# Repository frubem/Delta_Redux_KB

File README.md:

# DELTA Redux Keyboard

## DISCLAIMER

Any use of this project is **under your own responsibility**.
By using this project You will agree that I cannot be held responsible if it will destroy any of your devices, damage your computer, burn down your house or whatever.

### Sponsorship

This project is sponsored by [PCBWay](https://pcbway.com).
PCBWay specializes in manufacturing high-quality PCBs and makes them affordable to hobbyist and professionals alike.

The range of services they offer include PCB prototyping, assembly, instant quotes for your order, a verification process by a team
of experts and an easy to use, hassle-free order process.

Thanks to PCBWay, I was able to bring this project to production and to release it for everyone to use much earlier than it would have been possible otherwise.

## Introduction

This projects aims to create an ASCII keyboard tailored for use on to the [DELTA](https://codeberg.org/hkzlab/NE_Delta_Schematics) computer.
The work is based off the [Replica Datanetics Keyboard](https://github.com/schlae/replica-datanetics) by [Tube Time](https://mastodon.social/@tubetime), but sporting a different PCB, a modified circuit and firmware.

This keyboard supports uppercase and lowercase characters, both the strobe and AKD signals and caps-lock functionality (without using a mechanical latch), and can be built with your Cherry MX compatible switches of choice!

### Features

- Supports upper and lowercase characters
- Reset can be performed either with the reset button alone, or with the CTRL-Reset combination, depending on a jumper
- Caps lock without a mechanical latch
- Repeat key with adjustable frequency
- AKD signal
- External numeric keypad support
- 5 "extra" keys that can send custom strings to the attached machines

#### The "extra" keys

The "extra" keys are keys that simply trigger an automatic transmission of a string to the host computer, a macro. The strings are baked into the MCU, and the [firmware](fw/main.c) must be recompiled to change them.

The default strings are:
1. `PR#3\r`: Enables 80 column mode
2. `PR#6\r`: Boots card on slot 6
3. `CATALOG\r`: DOS command to list files on floppy
4. `CALL 65385\r`: When inside the BASIC interpreter, this will switch to the monitor
5. `03F4:00\rFA69G\r`: When inside the monitor, this will force a cold-reset

**Note that the optional numpad is still work-in-progress!**

### Support

If you wish to support me in building new hardware and software for old machines, [throw a few euros in my direction via Ko-Fi](https://ko-fi.com/hkzlab) ☕!

## Build one!

### Order the PCBs

You can find the gerbers in this repository, or you can order the PCBs at **PCBWay!**

You will one of each of the following:

- The [keyboard base](https://www.pcbway.com/project/shareproject/DELTA_Redux_ASCII_keyboard_0ab7f83a.html), where the switch and the circuitry solders to
- The [keyboard plate](https://www.pcbway.com/project/shareproject/DELTA_Keyboard_key_switch_plate_5280364c.html), where the switches are snapped into. Used to keep them stable
- The [IDC to DIP-16 adapter](https://www.pcbway.com/project/shareproject/DELTA_Keyboard_DIP_16_adapter_b9be4866.html). Unless you wish to use a DIP16 adapter directly on your IDC cable.

### Fixes

- [Keyboard](keyboard/fixes.md)

### Bill of Material

Every board directory contains a `bom.md` file containing the bill of material for the card.

Except for the plates: those are just support structure, nothing must be soldered to them.

- [Keyboard](keyboard/bom.md)
- [DIP-16 adapter](dip_adapter/bom.md)

## Thanks

- [TubeTime](https://mastodon.social/@tubetime) for the Datanetics replica I used as a base

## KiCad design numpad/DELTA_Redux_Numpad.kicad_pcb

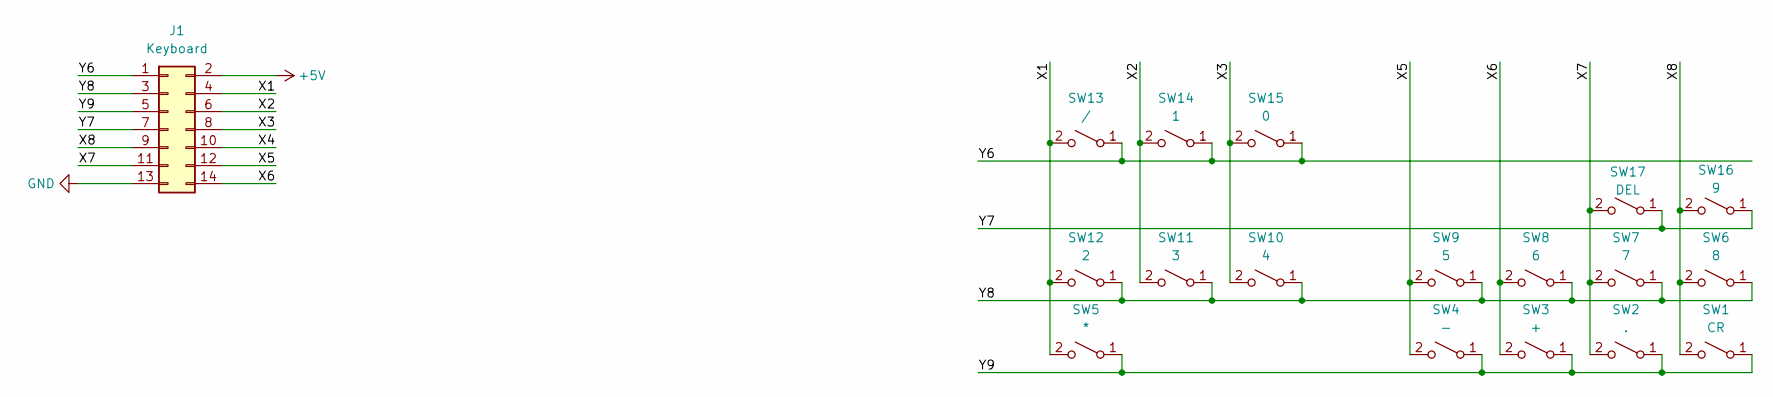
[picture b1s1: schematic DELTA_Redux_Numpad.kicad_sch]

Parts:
J1: Keyboard; PinHeader_2x07_P2.54mm_Horizontal
SW1: CR; SW_Cherry_MX_2.00u_PCB
SW2: .; SW_Cherry_MX_1.00u_PCB
SW3: +; SW_Cherry_MX_2.00u_PCB
SW4: -; SW_Cherry_MX_1.00u_PCB
SW5: *; SW_Cherry_MX_1.00u_PCB
SW6: 8; SW_Cherry_MX_1.00u_PCB
SW7: 7; SW_Cherry_MX_1.00u_PCB
SW8: 6; SW_Cherry_MX_1.00u_PCB
SW9: 5; SW_Cherry_MX_1.00u_PCB
SW10: 4; SW_Cherry_MX_1.00u_PCB
SW11: 3; SW_Cherry_MX_1.00u_PCB
SW12: 2; SW_Cherry_MX_1.00u_PCB
SW13: /; SW_Cherry_MX_1.00u_PCB
SW14: 1; SW_Cherry_MX_1.00u_PCB
SW15: 0; SW_Cherry_MX_2.00u_PCB
SW16: 9; SW_Cherry_MX_1.00u_PCB
SW17: DEL; SW_Cherry_MX_1.00u_PCB

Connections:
+5V: J1.2
/X1: J1.4, SW5.2 (B), SW12.2 (B), SW13.2 (B)
/X2: J1.6, SW11.2 (B), SW14.2 (B)
/X3: J1.8, SW10.2 (B), SW15.2 (B)
/X4: J1.10
/X5: J1.12, SW4.2 (B), SW9.2 (B)
/X6: J1.14, SW3.2 (B), SW8.2 (B)
/X7: J1.11, SW2.2 (B), SW7.2 (B), SW17.2 (B)
/X8: J1.9, SW1.2 (B), SW6.2 (B), SW16.2 (B)
/Y6: J1.1, SW13.1 (A), SW14.1 (A), SW15.1 (A)
/Y7: J1.7, SW16.1 (A), SW17.1 (A)
/Y8: J1.3, SW6.1 (A), SW7.1 (A), SW8.1 (A), SW9.1 (A), SW10.1 (A), SW11.1 (A), SW12.1 (A)
/Y9: J1.5, SW1.1 (A), SW2.1 (A), SW3.1 (A), SW4.1 (A), SW5.1 (A)
GND: J1.13

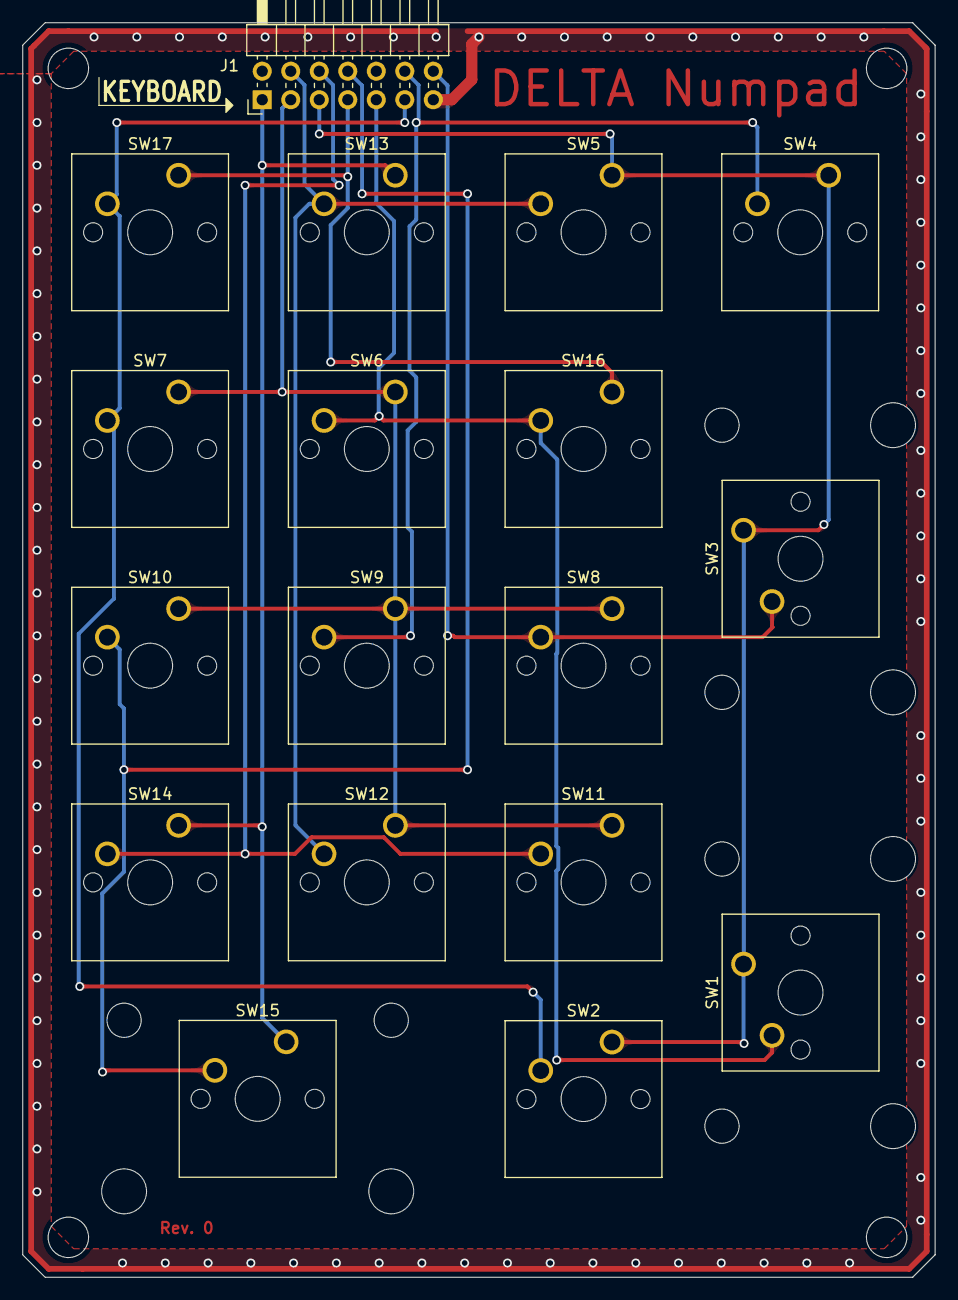
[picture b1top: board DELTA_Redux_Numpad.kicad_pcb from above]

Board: 2 copper layers, 81.3 x 111.8 mm, 18 parts (0 on the bottom side), 11 nets.

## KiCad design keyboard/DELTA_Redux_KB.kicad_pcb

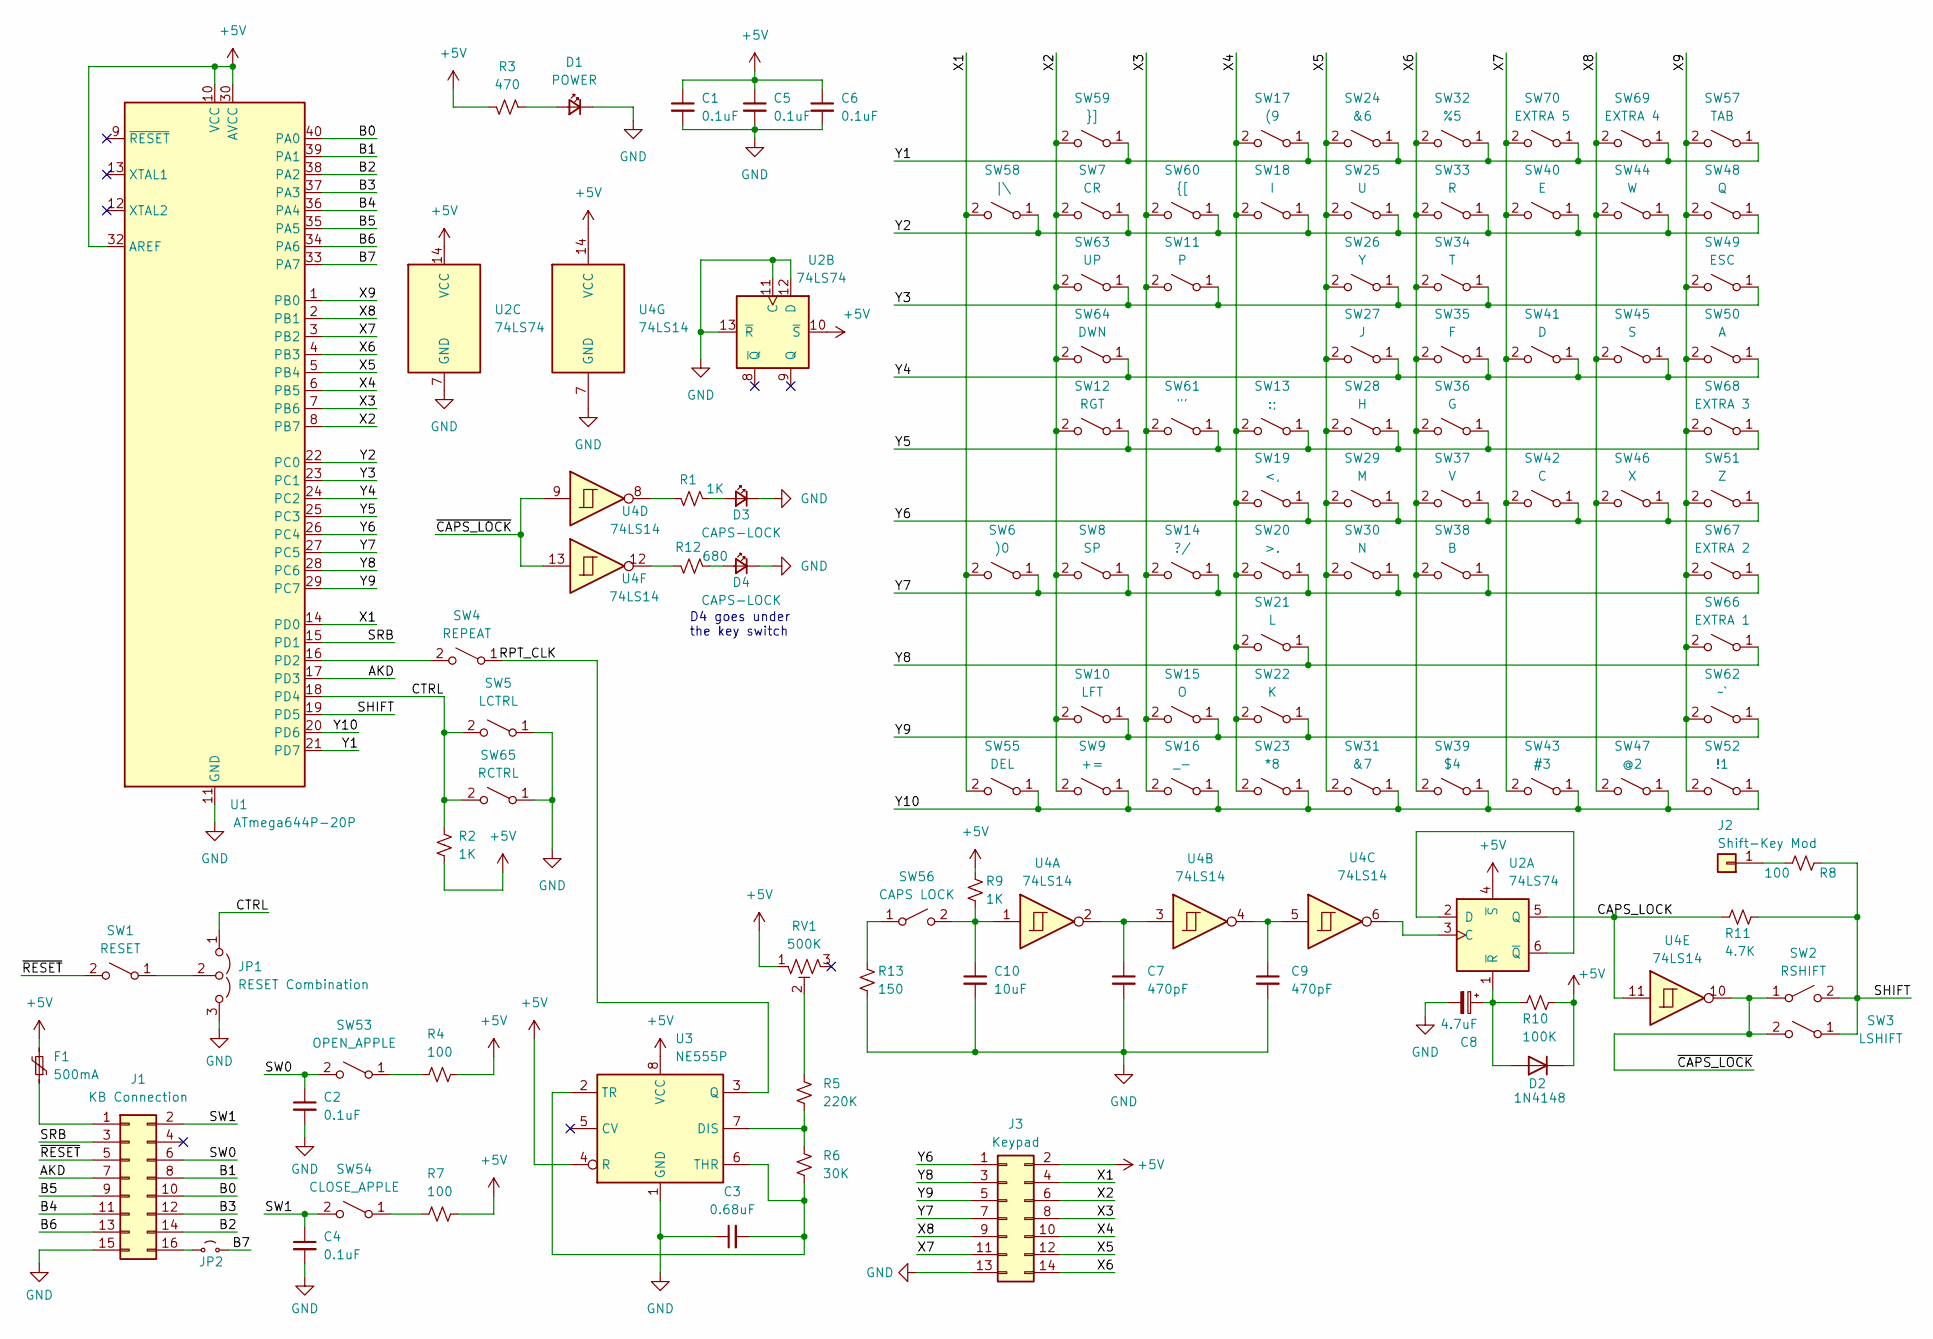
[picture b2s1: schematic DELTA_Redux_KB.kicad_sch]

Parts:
C1, C2, C4, C5, C6: 0.1uF; C_Disc_D5.0mm_W2.5mm_P5.00mm
C3: 0.68uF; C_Disc_D5.0mm_W2.5mm_P5.00mm
C7, C9: 470pF; C_Disc_D5.0mm_W2.5mm_P5.00mm
C8: 4.7uF; CP_Radial_D5.0mm_P2.50mm
C10: 10uF; C_Disc_D5.0mm_W2.5mm_P5.00mm
D1: POWER; LED_D5.0mm
D2: 1N4148; D_DO-35_SOD27_P10.16mm_Horizontal
D3: CAPS-LOCK; LED_D5.0mm
D4: CAPS-LOCK; LED_0603_1608Metric
F1: 500mA; Fuse_Bourns_MF-RHT070
J1: KB Connection; PinHeader_2x08_P2.54mm_Horizontal
J2: Shift-Key Mod; PinSocket_1x01_P2.54mm_Vertical
J3: Keypad; PinHeader_2x07_P2.54mm_Horizontal
JP1: RESET Combination; PinHeader_1x03_P2.54mm_Horizontal
JP2: Pass B8; PinSocket_1x02_P2.54mm_Vertical
R1, R2, R9: 1K; R_Axial_DIN0207_L6.3mm_D2.5mm_P10.16mm_Horizontal
R3: 470; R_Axial_DIN0207_L6.3mm_D2.5mm_P10.16mm_Horizontal
R4, R7, R8: 100; R_Axial_DIN0207_L6.3mm_D2.5mm_P10.16mm_Horizontal
R5: 220K; R_Axial_DIN0207_L6.3mm_D2.5mm_P10.16mm_Horizontal
R6: 30K; R_Axial_DIN0207_L6.3mm_D2.5mm_P10.16mm_Horizontal
R10: 100K; R_Axial_DIN0207_L6.3mm_D2.5mm_P10.16mm_Horizontal
R11: 4.7K; R_Axial_DIN0207_L6.3mm_D2.5mm_P10.16mm_Horizontal
R12: 680; R_Axial_DIN0207_L6.3mm_D2.5mm_P10.16mm_Horizontal
R13: 150; R_Axial_DIN0207_L6.3mm_D2.5mm_P10.16mm_Horizontal
RV1: 500K; Potentiometer_Bourns_3386F_Vertical
SW1: RESET; SW_Cherry_MX_1.00u_PCB
SW2: RSHIFT; SW_Cherry_MX_1.25u_PCB
SW3: LSHIFT; SW_Cherry_MX_2.25u_PCB
SW4: REPEAT; SW_Cherry_MX_1.00u_PCB
SW5: LCTRL; SW_Cherry_MX_1.50u_PCB
SW6: )0; SW_Cherry_MX_1.00u_PCB
SW7: CR; SW_Cherry_MX_1.75u_PCB
SW8: SP; SW_Cherry_MX_6.25u_PCB
SW9: +=; SW_Cherry_MX_1.00u_PCB
SW10: LFT; SW_Cherry_MX_1.00u_PCB
SW11: P; SW_Cherry_MX_1.00u_PCB
SW12: RGT; SW_Cherry_MX_1.00u_PCB
SW13: :;; SW_Cherry_MX_1.00u_PCB
SW14: ?/; SW_Cherry_MX_1.00u_PCB
SW15: O; SW_Cherry_MX_1.00u_PCB
SW16: _-; SW_Cherry_MX_1.00u_PCB
SW17: (9; SW_Cherry_MX_1.00u_PCB
SW18: I; SW_Cherry_MX_1.00u_PCB
SW19: <,; SW_Cherry_MX_1.00u_PCB
SW20: >.; SW_Cherry_MX_1.00u_PCB
SW21: L; SW_Cherry_MX_1.00u_PCB
SW22: K; SW_Cherry_MX_1.00u_PCB
SW23: *8; SW_Cherry_MX_1.00u_PCB
SW24: &6; SW_Cherry_MX_1.00u_PCB
SW25: U; SW_Cherry_MX_1.00u_PCB
SW26: Y; SW_Cherry_MX_1.00u_PCB
SW27: J; SW_Cherry_MX_1.00u_PCB
SW28: H; SW_Cherry_MX_1.00u_PCB
SW29: M; SW_Cherry_MX_1.00u_PCB
SW30: N; SW_Cherry_MX_1.00u_PCB
SW31: &7; SW_Cherry_MX_1.00u_PCB
SW32: %5; SW_Cherry_MX_1.00u_PCB
SW33: R; SW_Cherry_MX_1.00u_PCB
SW34: T; SW_Cherry_MX_1.00u_PCB
SW35: F; SW_Cherry_MX_1.00u_PCB
SW36: G; SW_Cherry_MX_1.00u_PCB
SW37: V; SW_Cherry_MX_1.00u_PCB
SW38: B; SW_Cherry_MX_1.00u_PCB
SW39: $4; SW_Cherry_MX_1.00u_PCB
SW40: E; SW_Cherry_MX_1.00u_PCB
SW41: D; SW_Cherry_MX_1.00u_PCB
SW42: C; SW_Cherry_MX_1.00u_PCB
SW43: #3; SW_Cherry_MX_1.00u_PCB
SW44: W; SW_Cherry_MX_1.00u_PCB
SW45: S; SW_Cherry_MX_1.00u_PCB
SW46: X; SW_Cherry_MX_1.00u_PCB
SW47: @2; SW_Cherry_MX_1.00u_PCB
SW48: Q; SW_Cherry_MX_1.00u_PCB
SW49: ESC; SW_Cherry_MX_1.00u_PCB
SW50: A; SW_Cherry_MX_1.00u_PCB
SW51: Z; SW_Cherry_MX_1.00u_PCB
SW52: !1; SW_Cherry_MX_1.00u_PCB
SW53: OPEN_APPLE; SW_Cherry_MX_1.50u_PCB
SW54: CLOSE_APPLE; SW_Cherry_MX_1.50u_PCB
SW55: DEL; SW_Cherry_MX_1.50u_PCB
SW56: CAPS LOCK; SW_Cherry_MX_1.75u_PCB
SW57: TAB; SW_Cherry_MX_1.50u_PCB
SW58: |\; SW_Cherry_MX_1.00u_PCB
SW59: }]; SW_Cherry_MX_1.00u_PCB
SW60: {[; SW_Cherry_MX_1.00u_PCB
SW61: "'; SW_Cherry_MX_1.00u_PCB
SW62: ~`; SW_Cherry_MX_1.00u_PCB
SW63: UP; SW_Cherry_MX_1.00u_PCB
SW64: DWN; SW_Cherry_MX_1.00u_PCB
SW65: RCTRL; SW_Cherry_MX_1.50u_PCB
SW66: EXTRA 1; SW_PUSH_6mm_H4.3mm
SW67: EXTRA 2; SW_PUSH_6mm_H4.3mm
SW68: EXTRA 3; SW_PUSH_6mm_H4.3mm
SW69: EXTRA 4; SW_PUSH_6mm_H4.3mm
SW70: EXTRA 5; SW_PUSH_6mm_H4.3mm
U1: ATmega644P-20P; DIP-40_W15.24mm
U2: 74LS74; DIP-14_W7.62mm
U3: NE555P; DIP-8_W7.62mm
U4: 74LS14; DIP-14_W7.62mm

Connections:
+5V: C1.1, C5.1, C6.1, D2.1 (K), F1.2, J3.2, R2.1, R3.1, R4.1, R7.1, R9.2, R10.2, RV1.1, U1.10 (VCC), U1.30 (AVCC), U1.32 (AREF), U2.4 (~S), U2.10 (~S), U2.14 (VCC), U3.4 (R), U3.8 (VCC), U4.14 (VCC)
/AKD: J1.7, U1.17 (PD3)
/B0: J1.10, U1.40 (PA0)
/B1: J1.8, U1.39 (PA1)
/B2: J1.14, U1.38 (PA2)
/B3: J1.12, U1.37 (PA3)
/B4: J1.11, U1.36 (PA4)
/B5: J1.9, U1.35 (PA5)
/B6: J1.13, U1.34 (PA6)
/B7: JP2.2 (B), U1.33 (PA7)
/CAPS_LOCK: R11.1, U2.5 (Q), U4.11
/CTRL: JP1.1 (A), R2.2, SW5.2 (B), SW65.2 (B), U1.18 (PD4)
/RPT_CLK: SW4.1 (A), U3.3 (Q)
/SHIFT: R8.2, R11.2, SW2.2 (B), SW3.1 (A), U1.19 (PD5)
/SRB: J1.3, U1.15 (PD1)
/SW0: C2.1, J1.6, SW53.2 (B)
/SW1: C4.1, J1.2, SW54.2 (B)
/X1: J3.4, SW6.2 (B), SW55.2 (B), SW58.2 (B), U1.14 (PD0)
/X2: J3.6, SW7.2 (B), SW8.2 (B), SW9.2 (B), SW10.2 (B), SW12.2 (B), SW59.2 (B), SW63.2 (B), SW64.2 (B), U1.8 (PB7)
/X3: J3.8, SW11.2 (B), SW14.2 (B), SW15.2 (B), SW16.2 (B), SW60.2 (B), SW61.2 (B), U1.7 (PB6)
/X4: J3.10, SW13.2 (B), SW17.2 (B), SW18.2 (B), SW19.2 (B), SW20.2 (B), SW21.2 (B), SW22.2 (B), SW23.2 (B), U1.6 (PB5)
/X5: J3.12, SW24.2 (B), SW25.2 (B), SW26.2 (B), SW27.2 (B), SW28.2 (B), SW29.2 (B), SW30.2 (B), SW31.2 (B), U1.5 (PB4)
/X6: J3.14, SW32.2 (B), SW33.2 (B), SW34.2 (B), SW35.2 (B), SW36.2 (B), SW37.2 (B), SW38.2 (B), SW39.2 (B), U1.4 (PB3)
/X7: J3.11, SW40.2 (B), SW41.2 (B), SW42.2 (B), SW43.2 (B), SW70.2 (B), U1.3 (PB2)
/X8: J3.9, SW44.2 (B), SW45.2 (B), SW46.2 (B), SW47.2 (B), SW69.2 (B), U1.2 (PB1)
/X9: SW48.2 (B), SW49.2 (B), SW50.2 (B), SW51.2 (B), SW52.2 (B), SW57.2 (B), SW62.2 (B), SW66.2 (B), SW67.2 (B), SW68.2 (B), U1.1 (PB0)
/Y1: SW17.1 (A), SW24.1 (A), SW32.1 (A), SW57.1 (A), SW59.1 (A), SW69.1 (A), SW70.1 (A), U1.21 (PD7)
/Y2: SW7.1 (A), SW18.1 (A), SW25.1 (A), SW33.1 (A), SW40.1 (A), SW44.1 (A), SW48.1 (A), SW58.1 (A), SW60.1 (A), U1.22 (PC0)
/Y3: SW11.1 (A), SW26.1 (A), SW34.1 (A), SW49.1 (A), SW63.1 (A), U1.23 (PC1)
/Y4: SW27.1 (A), SW35.1 (A), SW41.1 (A), SW45.1 (A), SW50.1 (A), SW64.1 (A), U1.24 (PC2)
/Y5: SW12.1 (A), SW13.1 (A), SW28.1 (A), SW36.1 (A), SW61.1 (A), SW68.1 (A), U1.25 (PC3)
/Y6: J3.1, SW19.1 (A), SW29.1 (A), SW37.1 (A), SW42.1 (A), SW46.1 (A), SW51.1 (A), U1.26 (PC4)
/Y7: J3.7, SW6.1 (A), SW8.1 (A), SW14.1 (A), SW20.1 (A), SW30.1 (A), SW38.1 (A), SW67.1 (A), U1.27 (PC5)
/Y8: J3.3, SW21.1 (A), SW66.1 (A), U1.28 (PC6)
/Y9: J3.5, SW10.1 (A), SW15.1 (A), SW22.1 (A), SW62.1 (A), U1.29 (PC7)
/Y10: SW9.1 (A), SW16.1 (A), SW23.1 (A), SW31.1 (A), SW39.1 (A), SW43.1 (A), SW47.1 (A), SW52.1 (A), SW55.1 (A), U1.20 (PD6)
/~CAPS_LOCK: SW2.1 (A), SW3.2 (B), U4.9, U4.10, U4.13
/~RESET: J1.5, SW1.2 (B)
GND: C1.2, C2.2, C3.1, C4.2, C5.2, C6.2, C7.2, C8.2, C9.2, C10.2, D1.1 (K), D3.1 (K), D4.1 (K), J1.15, J3.13, JP1.3 (B), R13.1, SW5.1 (A), SW65.1 (A), U1.11 (GND), U1.31 (GND), U2.7 (GND), U2.11 (C), U2.12 (D), U2.13 (~R), U3.1 (GND), U4.7 (GND)
unnamed: C7.1, U4.2, U4.3
unnamed: C9.1, U4.4, U4.5
unnamed: D1.2 (A), R3.2
unnamed: C8.1, D2.2 (A), R10.1, U2.1 (~R)
unnamed: D3.2 (A), R1.2
unnamed: D4.2 (A), R12.2
unnamed: F1.1, J1.1
unnamed: J1.16, JP2.1 (A)
unnamed: J2.1, R8.1
unnamed: JP1.2 (C), SW1.1 (A)
unnamed: R1.1, U4.8
unnamed: R5.2, RV1.2
unnamed: R12.1, U4.12
unnamed: SW4.2 (B), U1.16 (PD2)
unnamed: R4.2, SW53.1 (A)
unnamed: R7.2, SW54.1 (A)
unnamed: R13.2, SW56.1 (A)
unnamed: C10.1, R9.1, SW56.2 (B), U4.1
unnamed: U2.3 (C), U4.6
unnamed: U2.2 (D), U2.6 (~Q)
unnamed: R5.1, R6.2, U3.7 (DIS)
unnamed: C3.2, R6.1, U3.2 (TR), U3.6 (THR)

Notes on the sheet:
D4 goes under the key switch

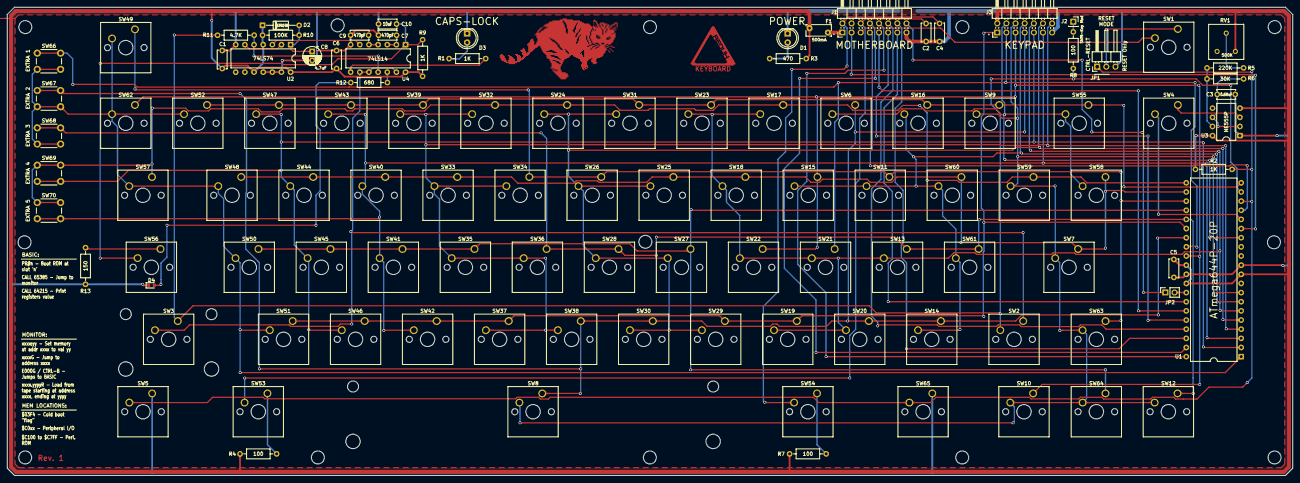
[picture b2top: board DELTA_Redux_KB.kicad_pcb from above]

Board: 2 copper layers, 356.9 x 130.0 mm, 108 parts (0 on the bottom side), 61 nets.
